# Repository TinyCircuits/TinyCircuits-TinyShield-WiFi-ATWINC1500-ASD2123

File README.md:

# TinyCircuits TinyShield WiFi ATWINC1500 Board
# ASD2123 Rev1

These are the design files for the TinyCircuits ASD2123 Rev 1 PCB.  This is a TinyShield board that has a Atmel ATWINC1500 WiFi module, local power supply and level shifters to connect between the TinyDuino and the WiFi Module. 

Format is in Cadsoft Eagle format - Eagle version 6.2 was used for the original design.

For more infomation on this, check out the product page at TinyCircuits.com:  https://tinycircuits.com/products/wifi-tinyshield-atwinc1500

# License:

Design by TinyCircuits.
All design files are released under the Creative Commons Attribution Share-Alike 3.0 License, see the following link for details: http://creativecommons.org/licenses/by-sa/3.0

All text above must be included in any redistribution or derived design

This project uses designs and concepts developed as part of the Arduino project and the LilyPad project.  The TinyCircuits design files themselves (schematics, PCB and libraries) are not directly derived from these works' design files and have been created new, however the concepts and basic architecture behind the TinyDuino and TinyLily products are derived and we thank the hard work of the organizations below for their contributions to open-source hardware:
  
Original Arduino Uno Design by Team Arduino

LilyPad Arduino Design by Leah Buechley and Sparkfun Electronics

Please support the open-source hardware community

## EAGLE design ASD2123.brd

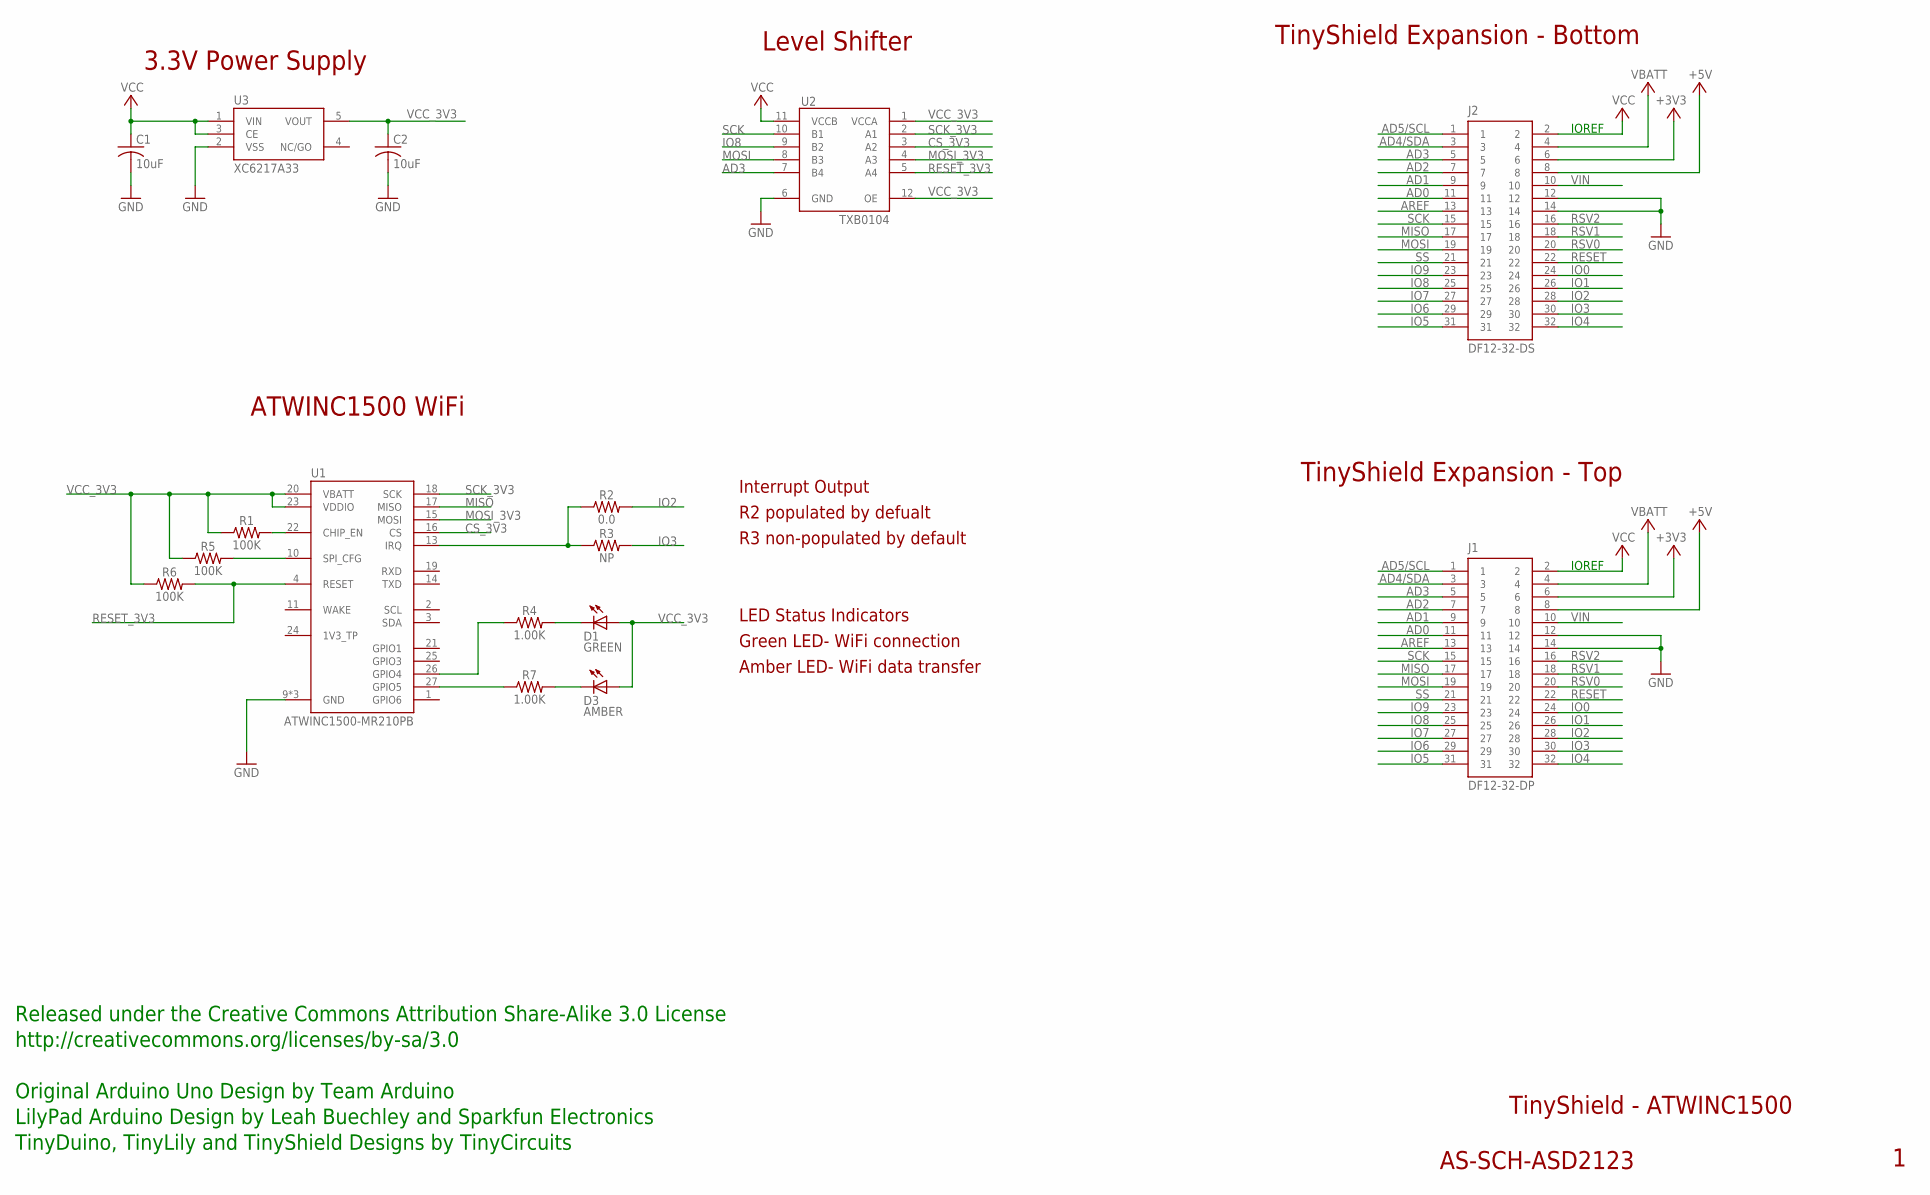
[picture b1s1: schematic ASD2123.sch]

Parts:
C1, C2: 10uF; C0603; PARTNO AS-ITM-00002
D1: GREEN; 0402_LED
D3: AMBER; 0402_LED
J1: DF12-32-DP; PARTNO AS-ITM-00015
J2: DF12-32-DS; PARTNO AS-ITM-00012
R1, R5, R6: 100K; 0402
R2: 0.0; 0402; PARTNO AS-ITM-00076
R3: NP; 0402; PARTNO AS-ITM-00076
R4, R7: 1.00K; 0402
U1: ATWINC1500-MR210PB
U2: TXB0104; UQFN-12
U3: XC6217A33; SOT-25; PARTNO AS-ITM-00046

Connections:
+3V3: J1.6, J2.6
+5V: J1.8, J2.8
AD0: J1.11, J2.11
AD1: J1.9, J2.9
AD2: J1.7, J2.7
AD3: J1.5, J2.5, U2.7 (B4)
AD4/SDA: J1.3, J2.3
AD5/SCL: J1.1, J2.1
AREF: J1.13, J2.13
CS_3V3: U1.16 (CS), U2.3 (A2)
GND: C1.2, C2.2, J1.12, J1.14, J2.12, J2.14, U1.9 (GND), U1.12 (GND), U1.28 (GND), U2.6 (GND), U3.2 (VSS)
IO0: J1.24, J2.24
IO1: J1.26, J2.26
IO2: J1.28, J2.28, R2.2
IO3: J1.30, J2.30, R3.2
IO4: J1.32, J2.32
IO5: J1.31, J2.31
IO6: J1.29, J2.29
IO7: J1.27, J2.27
IO8: J1.25, J2.25, U2.9 (B2)
IO9: J1.23, J2.23
IRQ: R2.1, R3.1, U1.13 (IRQ)
MISO: J1.17, J2.17, U1.17 (MISO)
MOSI: J1.19, J2.19, U2.8 (B3)
MOSI_3V3: U1.15 (MOSI), U2.4 (A3)
unnamed: R1.2, U1.22 (CHIP_EN)
unnamed: R4.1, U1.26 (GPIO4)
unnamed: R7.1, U1.27 (GPIO5)
unnamed: R5.2, U1.10 (SPI_CFG)
unnamed: D1.2 (C), R4.2
unnamed: D3.2 (C), R7.2
RESET: J1.22, J2.22
RESET_3V3: R6.2, U1.4 (RESET), U2.5 (A4)
RSV0: J1.20, J2.20
RSV1: J1.18, J2.18
RSV2: J1.16, J2.16
SCK: J1.15, J2.15, U2.10 (B1)
SCK_3V3: U1.18 (SCK), U2.2 (A1)
SS: J1.21, J2.21
VBATT: J1.4, J2.4
VCC: C1.1, J1.2, J2.2, U2.11 (VCCB), U3.1 (VIN), U3.3 (CE)
VCC_3V3: C2.1, D1.1 (A), D3.1 (A), R1.1, R5.1, R6.1, U1.20 (VBATT), U1.23 (VDDIO), U2.1 (VCCA), U2.12 (OE), U3.5 (VOUT)
VIN: J1.10, J2.10

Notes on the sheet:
TinyShield Expansion - Bottom
TinyShield - ATWINC1500
AS-SCH-ASD2123
TinyShield Expansion - Top
IOREF
Released under the Creative Commons Attribution Share-Alike 3.0 License
http://creativecommons.org/licenses/by-sa/3.0
LilyPad Arduino Design by Leah Buechley and Sparkfun Electronics
TinyDuino, TinyLily and TinyShield Designs by TinyCircuits
Original Arduino Uno Design by Team Arduino
3.3V Power Supply
ATWINC1500 WiFi
Level Shifter
Interrupt Output
R2 populated by defualt
R3 non-populated by default
LED Status Indicators
Green LED- WiFi connection
Amber LED- WiFi data transfer

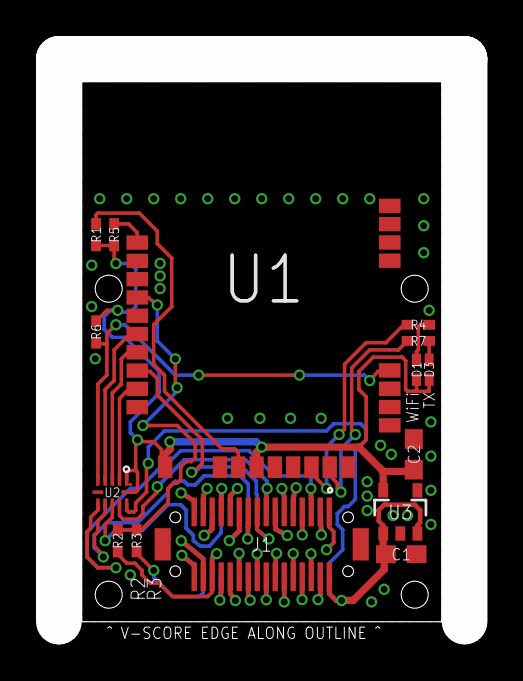
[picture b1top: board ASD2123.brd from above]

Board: 2 copper layers, 20.0 x 30.0 mm, 17 parts (1 on the bottom side), 43 nets.

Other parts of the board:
U$1: DOCFIELD-TINYCIRCUITS-PCB

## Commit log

2017-01-31 :lollipop: Added .gitattributes & .gitignore files
2019-01-02 update format
2019-01-07 updated comments
2019-02-01 add tutorial images
2019-02-01 add zip file
2019-05-13 update images
2019-05-20 updated naming
2019-05-22 added images
2019-05-23 updated images
2019-05-23 added .zip files
2020-02-11 image update
2020-04-13 fix brackets
2020-07-28 Add CAD data
2020-08-14 Update CAD drawing
2023-03-25 2.4GHz network clarification
2023-03-25 Print message with newline
    It's more clear that things are working when a new line is printer rather then when it appends to the right ;-)
    I'm hoping that you've got automation which will update the .zip file?
